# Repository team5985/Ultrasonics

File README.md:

# Ultrasonics
Ultrasonic hardware and software

This contains the design files for the ultrasonics circuit boards, as well as the software for the microcontroller.

* Hardware
These are the project files from KiCAD and include the circuit diagramme, netlist, and PCB layout. The Gerber directory
contains the final output that was sent to the PCB manufacturer to have the boards made. This should be openable as a
project from within KiCAD.

* Software
These are the project files from AVR Studio (or ATMEL Studio, or Microchip Studio) and contain the setup required to
compile, emulate and debug the microcontroller code. This should be able to be opened by AVR Studio as a project and
used immediately. The main file in this is "main.asm" which is the actual code for the microcontroller, the remaining
files are merely configuration.

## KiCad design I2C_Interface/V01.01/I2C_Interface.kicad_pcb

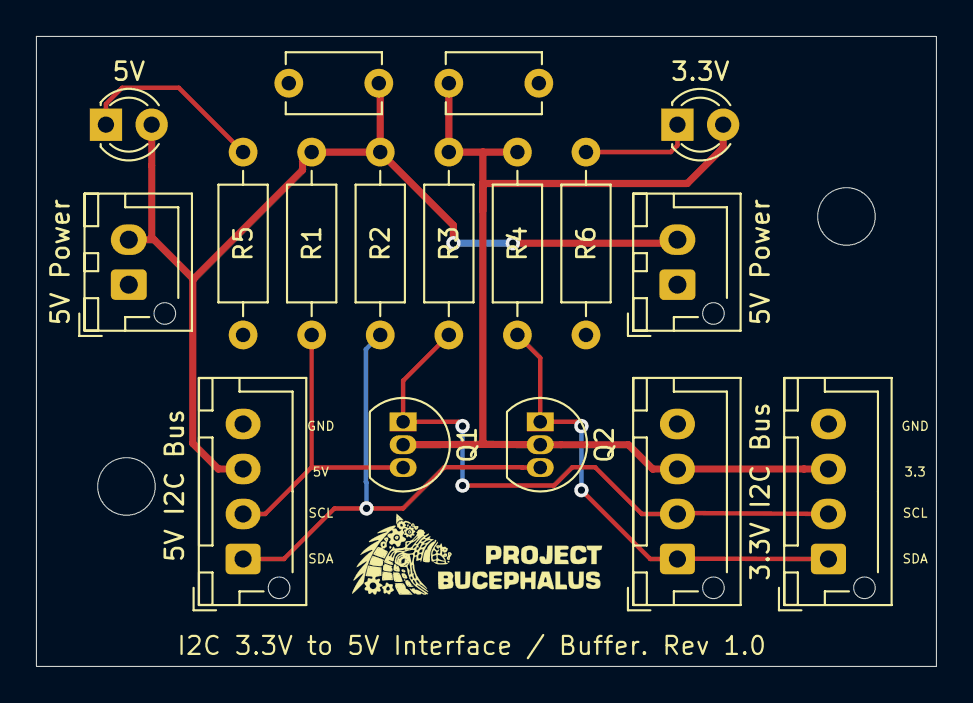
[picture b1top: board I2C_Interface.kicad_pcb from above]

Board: 2 copper layers, 50.0 x 35.0 mm, 17 parts (0 on the bottom side), 9 nets.

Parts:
3.3V, 5V: LED; LED_D3.0mm
C1, C2: 4.7uF; C_Disc_D5.1mm_W3.2mm_P5.00mm
J1, J3: 3.3V I2C Bus; JST_XH_B4B-XH-AM_1x04_P2.50mm_Vertical
J2, J5: 5V Power; JST_XH_B2B-XH-AM_1x02_P2.50mm_Vertical
J4: 5V I2C Bus; JST_XH_B4B-XH-AM_1x04_P2.50mm_Vertical
Q1, Q2: 2N7000; TO-92_Inline
R1, R2, R3, R4: 33k; R_Axial_DIN0207_L6.3mm_D2.5mm_P10.16mm_Horizontal
R5: 200R; R_Axial_DIN0207_L6.3mm_D2.5mm_P10.16mm_Horizontal
R6: 82R; R_Axial_DIN0207_L6.3mm_D2.5mm_P10.16mm_Horizontal

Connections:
+3V3: 3.3V.2, C2.1, J1.3, J3.3, Q1.2, Q2.2, R3.2, R4.2
+5V: 5V.2, C1.2, J2.2, J4.3, J5.2, R1.2, R2.2
GND: C1.1, C2.2, J1.4, J2.1, J3.4, J4.4, J5.1, R5.1, R6.1
unnamed: 3.3V.1, R6.2
unnamed: 5V.1, R5.2
unnamed: J1.1, J3.1, Q2.1, R4.1
unnamed: J1.2, J3.2, Q1.1, R3.1
unnamed: J4.1, Q2.3, R2.1
unnamed: J4.2, Q1.3, R1.1

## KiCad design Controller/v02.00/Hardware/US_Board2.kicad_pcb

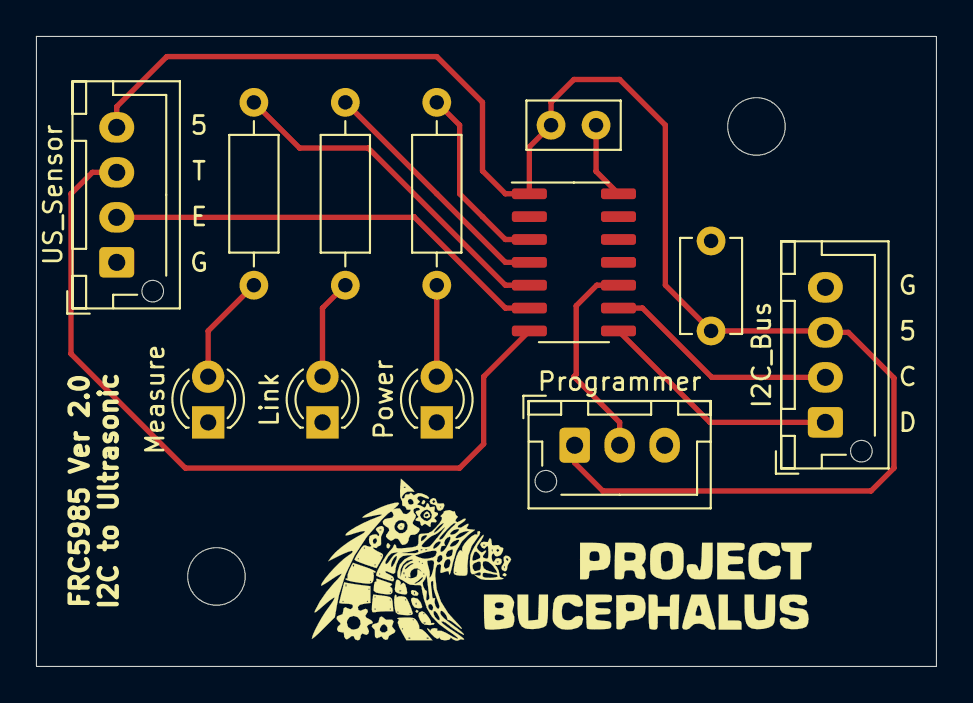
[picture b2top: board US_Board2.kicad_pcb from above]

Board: 2 copper layers, 50.0 x 35.0 mm, 12 parts (0 on the bottom side), 13 nets.

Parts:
200R1, 200R2, 200R3: R; R_Axial_DIN0207_L6.3mm_D2.5mm_P10.16mm_Horizontal
C1: 4.7uF; C_Disc_D5.1mm_W3.2mm_P5.00mm
C2: 100nF; C_Disc_D5.0mm_W2.5mm_P2.50mm
I2C_Bus: Conn_01x04_Male; JST_XH_B4B-XH-AM_1x04_P2.50mm_Vertical
Link: Yellow LED; LED_D3.0mm
Measure: Green LED; LED_D3.0mm
Power: Red LED; LED_D3.0mm
Programmer: Conn_01x03; JST_XH_B3B-XH-AM_1x03_P2.50mm_Vertical
U1: ATtiny214-SS; SOIC-14_3.9x8.7mm_P1.27mm
US_Sensor: Conn_01x04_Male; JST_XH_B4B-XH-AM_1x04_P2.50mm_Vertical

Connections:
+5V: C1.1, C2.1, I2C_Bus.3, Programmer.1, U1.1, US_Sensor.4
GND: C1.2, C2.2, I2C_Bus.4, Link.1, Measure.1, Power.1, Programmer.3, U1.14, US_Sensor.1
unnamed: 200R1.1, Link.2
unnamed: 200R1.2, U1.4
unnamed: 200R2.1, Power.2
unnamed: 200R2.2, U1.3
unnamed: 200R3.1, Measure.2
unnamed: 200R3.2, U1.5
unnamed: I2C_Bus.1, U1.8
unnamed: I2C_Bus.2, U1.9
unnamed: Programmer.2, U1.10
unnamed: U1.6, US_Sensor.2
unnamed: U1.7, US_Sensor.3

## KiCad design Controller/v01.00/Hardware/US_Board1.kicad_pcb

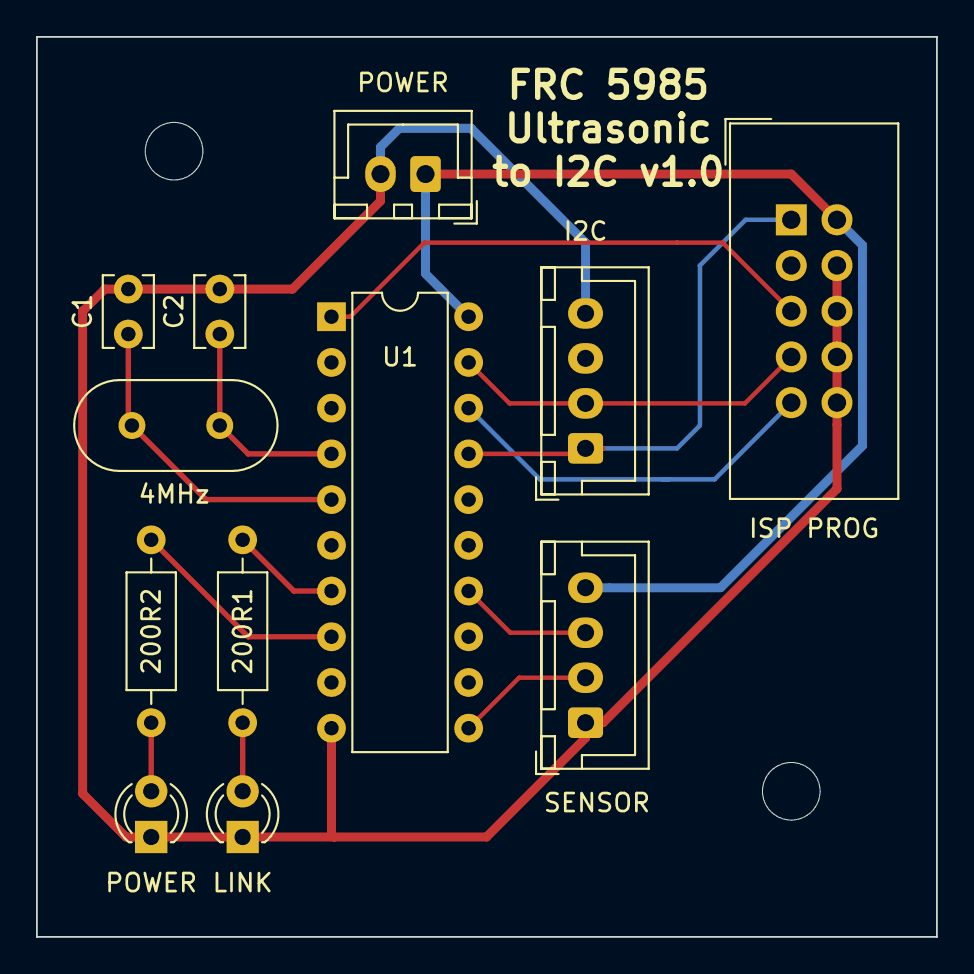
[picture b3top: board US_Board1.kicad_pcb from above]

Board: 2 copper layers, 50.0 x 50.0 mm, 14 parts (0 on the bottom side), 14 nets.

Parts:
4MHz: Crystal; Crystal_HC49-U_Vertical
200R1, 200R2: R; R_Axial_DIN0207_L6.3mm_D2.5mm_P10.16mm_Horizontal
 : MountingHole_3.2mm_M3_DIN965
 #2: MountingHole_3.2mm_M3_DIN965
C1, C2: C; C_Disc_D3.8mm_W2.6mm_P2.50mm
I2C: Conn_01x04_Male; JST_XH_B4B-XH-A_1x04_P2.50mm_Vertical
ISP PROG: AVR-ISP-10; IDC-Header_2x05_P2.54mm_Vertical
LINK: Yellow LED; LED_D3.0mm
POWER: Conn_01x02_Male; JST_XH_B2B-XH-A_1x02_P2.50mm_Vertical
POWER#2: Red LED; LED_D3.0mm
SENSOR: Conn_01x04_Male; JST_XH_B4B-XH-A_1x04_P2.50mm_Vertical
U1: ATtiny2313-20PU; DIP-20_W7.62mm

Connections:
+5V: ISP PROG.2, POWER.1, SENSOR.4, U1.20
GND: C1.2, C2.2, I2C.4, ISP PROG.4, ISP PROG.6, ISP PROG.8, ISP PROG.10, LINK.1, POWER.2, POWER#2.1, SENSOR.1, U1.10
unnamed: 4MHz.1, C1.1, U1.5
unnamed: 4MHz.2, C2.1, U1.4
unnamed: 200R1.1, LINK.2
unnamed: 200R1.2, U1.7
unnamed: 200R2.1, POWER#2.2
unnamed: 200R2.2, U1.8
unnamed: I2C.1, ISP PROG.1, U1.17
unnamed: I2C.2, ISP PROG.7, U1.19
unnamed: ISP PROG.5, U1.1
unnamed: ISP PROG.9, U1.18
unnamed: SENSOR.2, U1.11
unnamed: SENSOR.3, U1.14

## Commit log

2022-01-07 Create temp
